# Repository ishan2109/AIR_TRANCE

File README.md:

# IR_TRANCE
Quadcopter
PS-This is an ongoing project.Anyone who views this or clones the files will have to make changes to the code.

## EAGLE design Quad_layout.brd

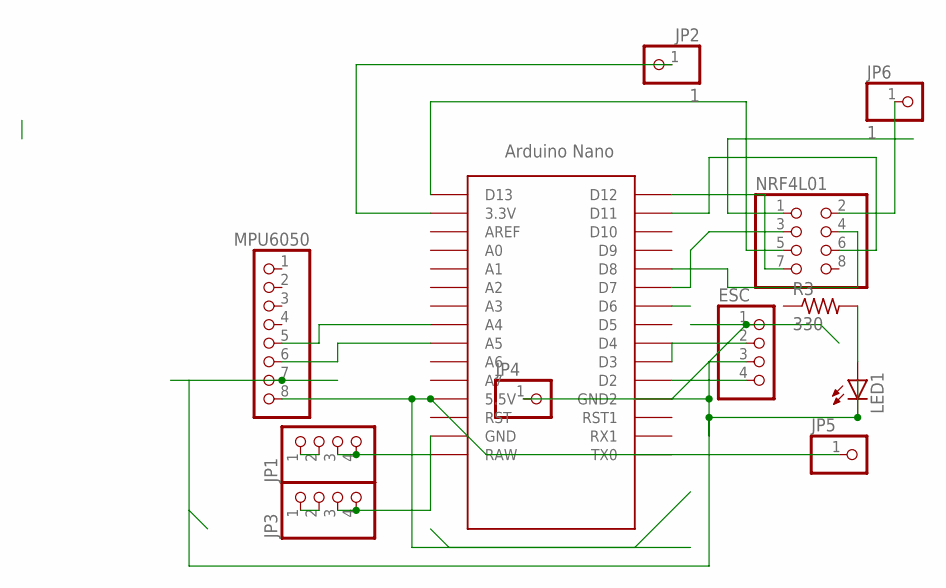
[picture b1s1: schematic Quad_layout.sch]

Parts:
ESC: PINHD-1X4; 1X04
JP1, JP3: PINHD-1X4; 1X04
JP2, JP6: 1; 1X01
JP4, JP5: PINHD-1X1; 1X01
LED1: LED3MM
MPU6050: PINHD-1X8; 1X08
NRF4L01: PINHD-2X4; 2X04
R3: 330; 0207/10
U$1: NANO

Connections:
unnamed: NRF4L01.4, U$1.D8
unnamed: NRF4L01.6, U$1.D11
unnamed: JP5.1, MPU6050.8, U$1.5V (5.5V)
unnamed: JP1.3, JP1.4, U$1.RAW
unnamed: ESC.4, LED1.K (C), MPU6050.7, U$1.GND1 (GND2)
unnamed: JP1.1, JP1.2
unnamed: ESC.2, U$1.D3
unnamed: ESC.3, U$1.D2
unnamed: ESC.1, JP4.1
unnamed: JP3.3, JP3.4, U$1.GND
unnamed: NRF4L01.7, U$1.D12
unnamed: JP3.1, JP3.2
unnamed: LED1.A, R3.2
unnamed: JP6.1, NRF4L01.2
unnamed: NRF4L01.5, U$1.D13
unnamed: JP2.1, U$1.3.3V
unnamed: MPU6050.5, U$1.A4
unnamed: MPU6050.6, U$1.A5

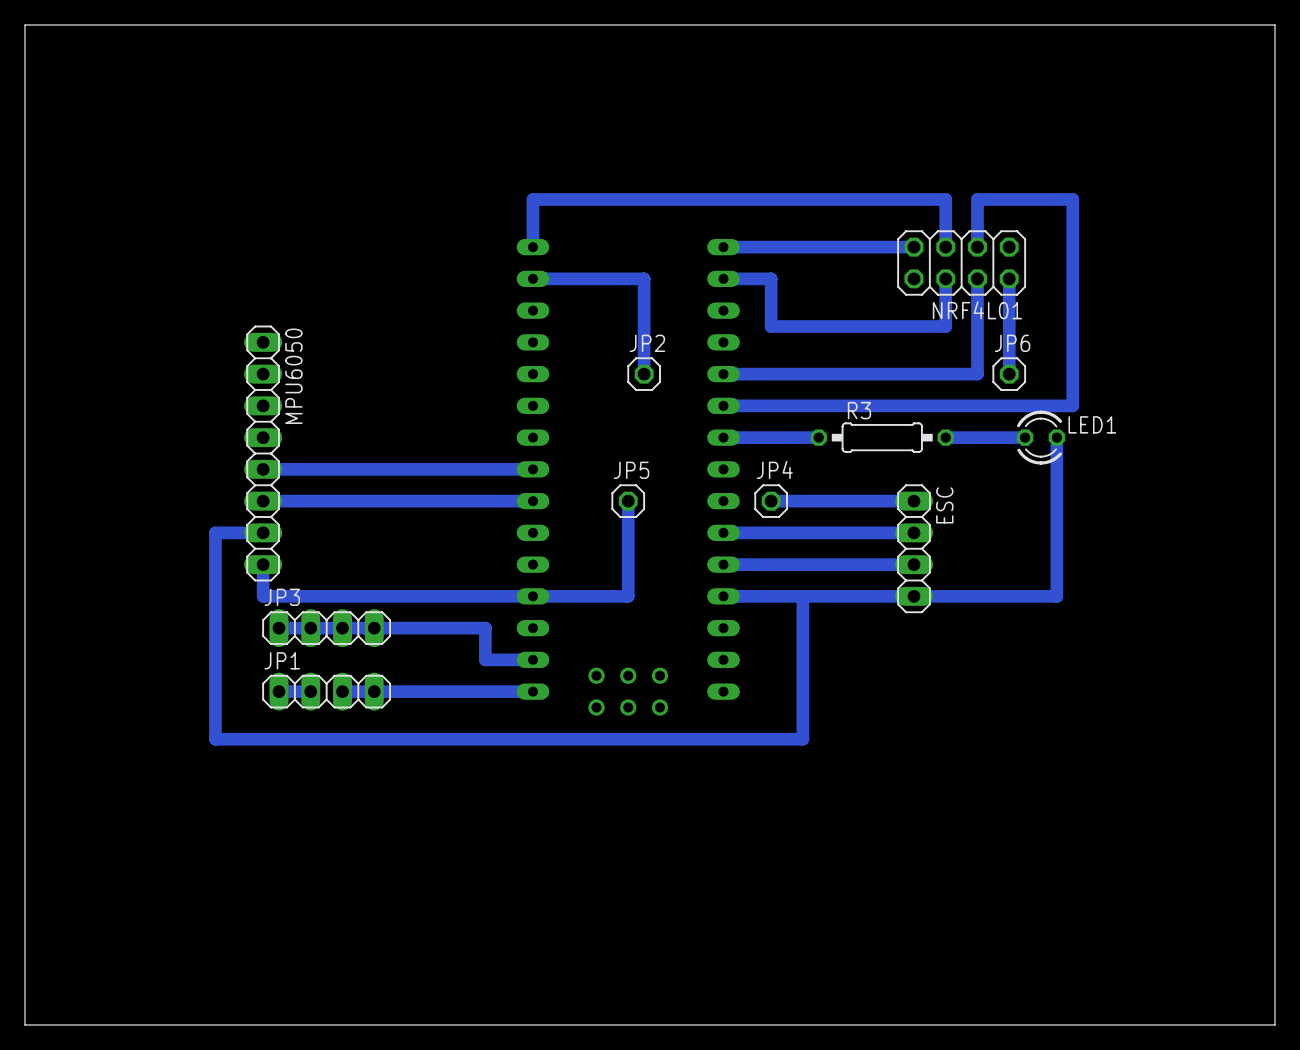
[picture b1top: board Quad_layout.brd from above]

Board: 2 copper layers, 100.0 x 80.0 mm, 12 parts (0 on the bottom side), 18 nets.
